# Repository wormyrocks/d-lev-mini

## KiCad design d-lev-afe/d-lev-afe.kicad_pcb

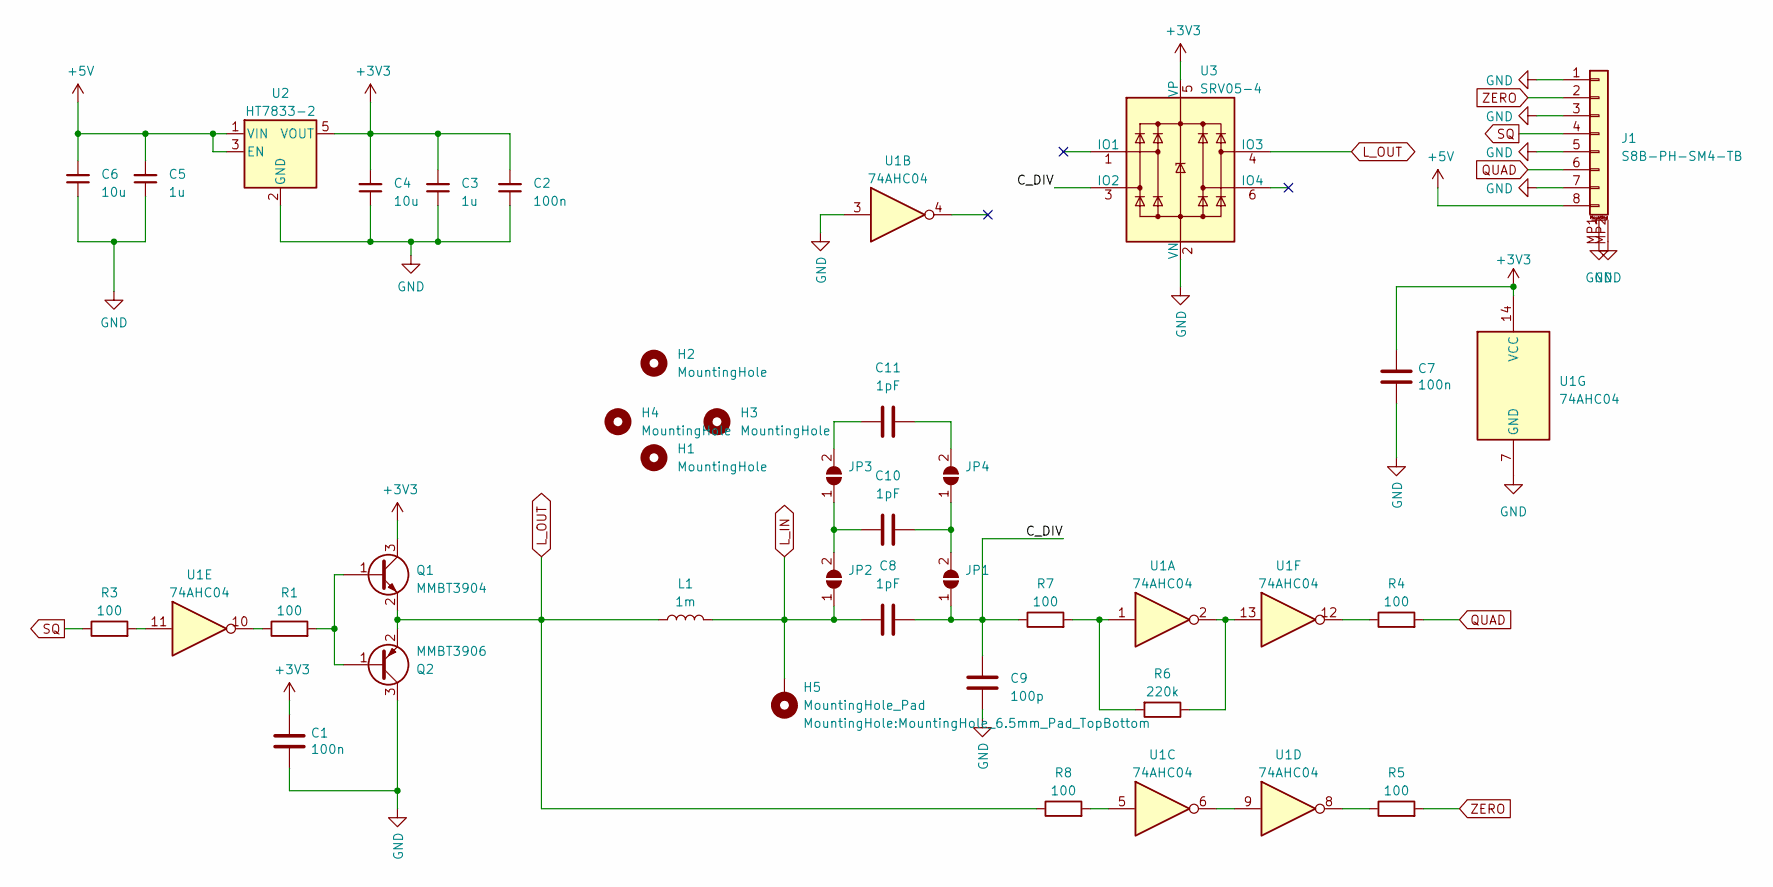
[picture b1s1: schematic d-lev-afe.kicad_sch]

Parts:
C1, C2, C7: 100n; C_0603_1608Metric; MPN GRM188R71E104KA01D; LCSC C14663
C3, C5: 1u; C_0603_1608Metric; LCSC C15849
C4, C6: 10u; C_0805_2012Metric; MPN CL21A106KAYNNNG; LCSC C440198
C8, C10, C11: 1pF; testpoint_cap_1pf
C9: 100p; C_0603_1608Metric; MPN C0603C101K8RACAUTO; LCSC C14858
H1, H2, H3, H4: MountingHole; MountingHole_3.2mm_M3
H5: MountingHole_Pad; MountingHole_6.5mm_Pad_TopBottom
J1: S8B-PH-SM4-TB; JST_PH_S8B-PH-SM4-TB_1x08-1MP_P2.00mm_Horizontal; MPN S8B-PH-SM4-TB; LCSC C265121
JP1, JP2, JP3, JP4: SolderJumper_2_Open; SolderJumper-0.5mm-Tiny
L1: 1m; LargeHoneycombCoil; Tolerance 10%; MPN 2ZFF4-252k-DM
Q1: MMBT3904; SOT-23; MPN MMBT3904-7-F; LCSC C20526
Q2: MMBT3906; SOT-23; MPN MMBT3906-7-F; LCSC C2143
R1, R3, R4, R5, R7, R8: 100; R_0603_1608Metric; LCSC C22775
R6: 220k; R_0603_1608Metric; MPN RC0603FR-13220KL; LCSC C22961
U1: 74AHC04; SOIC-14_3.9x8.7mm_P1.27mm; MPN SN74AHC04DRG4; LCSC C8131
U2: HT7833-2; SOT-23-5; MPN HT7833-2; LCSC C164106
U3: SRV05-4; SOT-23-6; MPN SRV05-4L-TP; LCSC C85364

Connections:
+3V3: C1.1, C2.2, C3.2, C4.2, C7.1, Q1.3 (C), U1.14 (VCC), U2.5 (VOUT), U3.5 (VP)
+5V: C5.2, C6.2, J1.8, U2.1 (VIN), U2.3 (EN)
/C_DIV: C8.1, C9.1, JP1.1 (A), R7.1, U3.3 (IO2)
GND: C1.2, C2.1, C3.1, C4.1, C5.1, C6.1, C7.2, C9.2, J1.1, J1.3, J1.5, J1.7, J1.MP1 (MountPin1), J1.MP2 (MountPin2), Q2.3 (C), U1.3, U1.7 (GND), U2.2 (GND), U3.2 (VN)
L_IN: C8.2, H5.1, JP2.1 (A), L1.2
L_OUT: L1.1, Q1.2 (E), Q2.2 (E), R8.1, U3.4 (IO3)
unnamed: C10.1, JP1.2 (B), JP4.1 (A)
unnamed: C10.2, JP2.2 (B), JP3.1 (A)
unnamed: C11.2, JP3.2 (B)
unnamed: C11.1, JP4.2 (B)
unnamed: Q1.1 (B), Q2.1 (B), R1.2
unnamed: R1.1, U1.10
unnamed: R3.2, U1.11
unnamed: R4.1, U1.12
unnamed: R5.1, U1.8
unnamed: R6.1, U1.2, U1.13
unnamed: R6.2, R7.2, U1.1
unnamed: R8.2, U1.5
unnamed: U1.6, U1.9
QUAD: J1.6, R4.2
SQ: J1.4, R3.1
ZERO: J1.2, R5.2

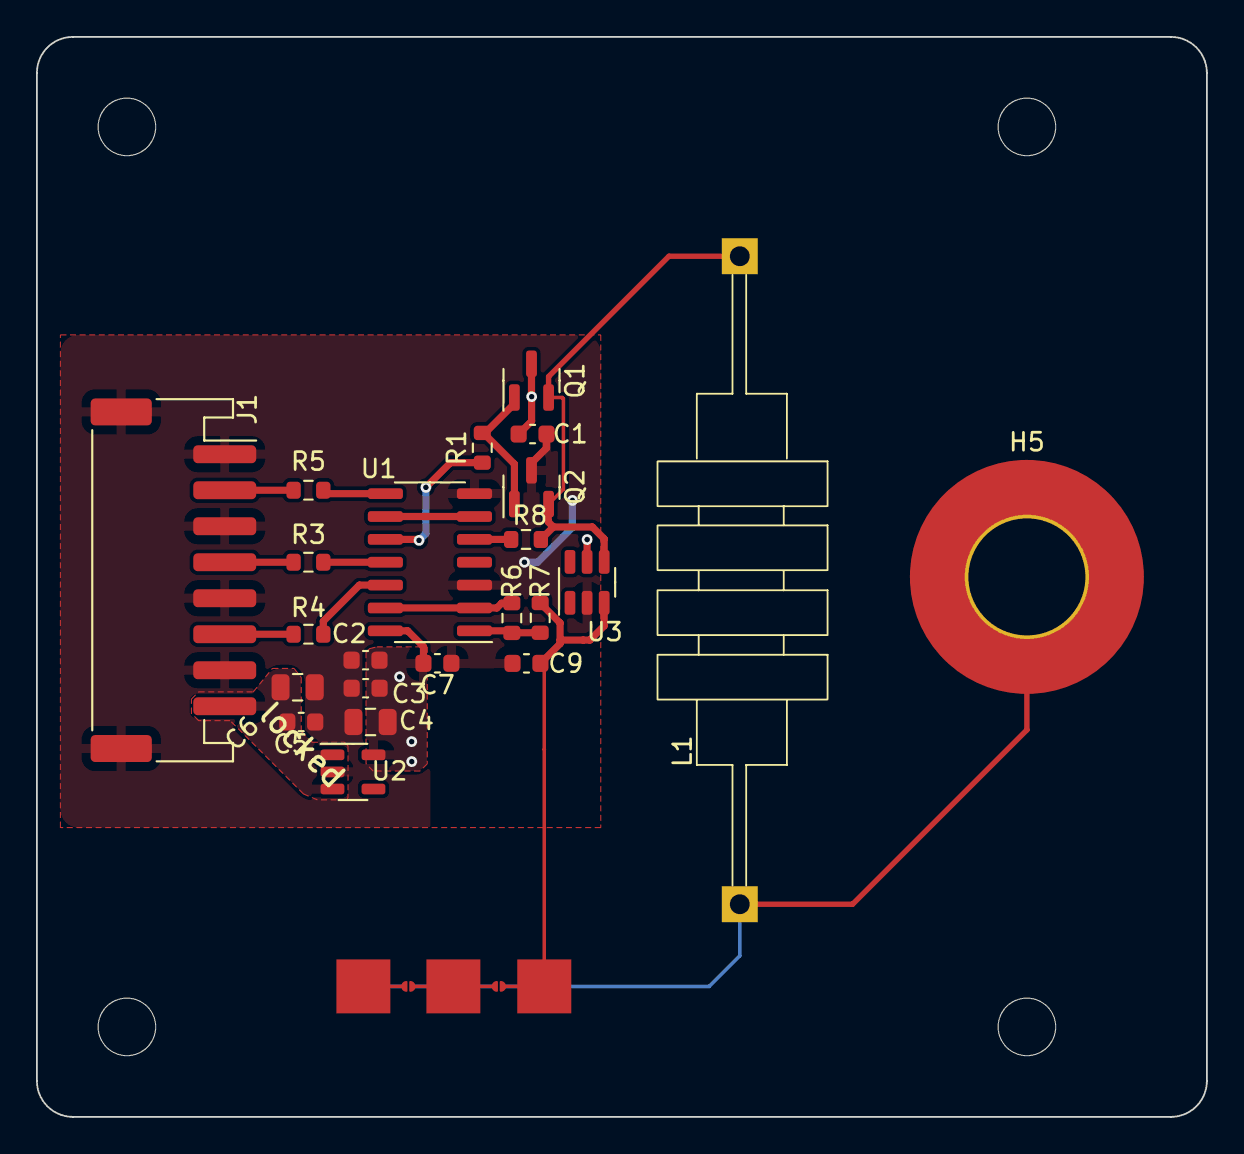
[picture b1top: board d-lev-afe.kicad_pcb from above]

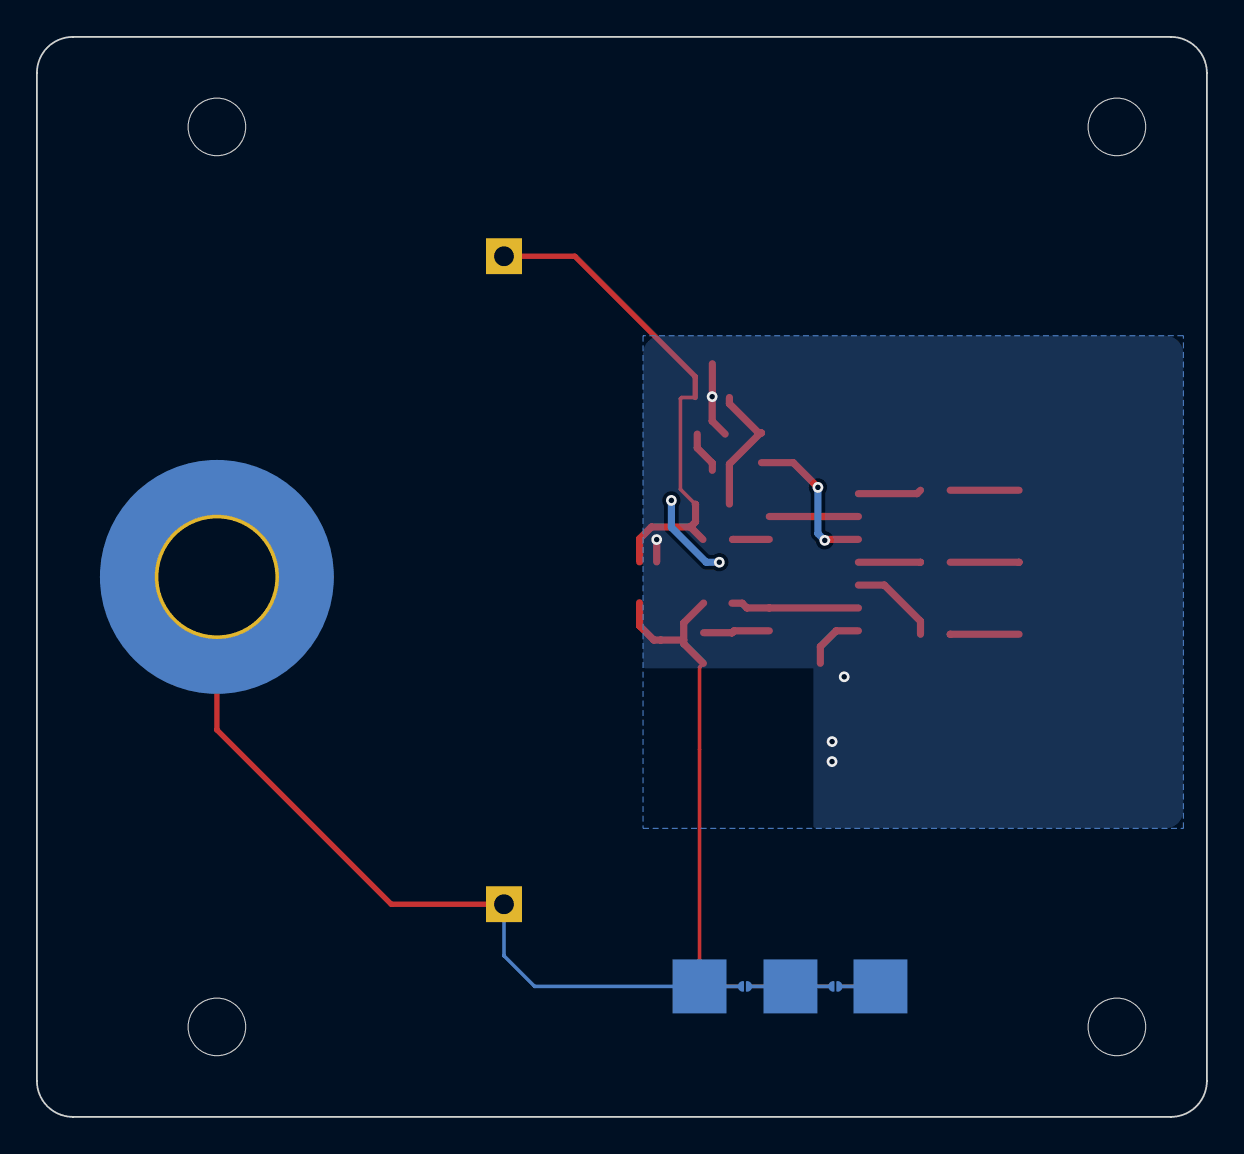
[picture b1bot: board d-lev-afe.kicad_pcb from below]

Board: 2 copper layers, 65.0 x 60.0 mm, 34 parts (2 on the bottom side), 22 nets.

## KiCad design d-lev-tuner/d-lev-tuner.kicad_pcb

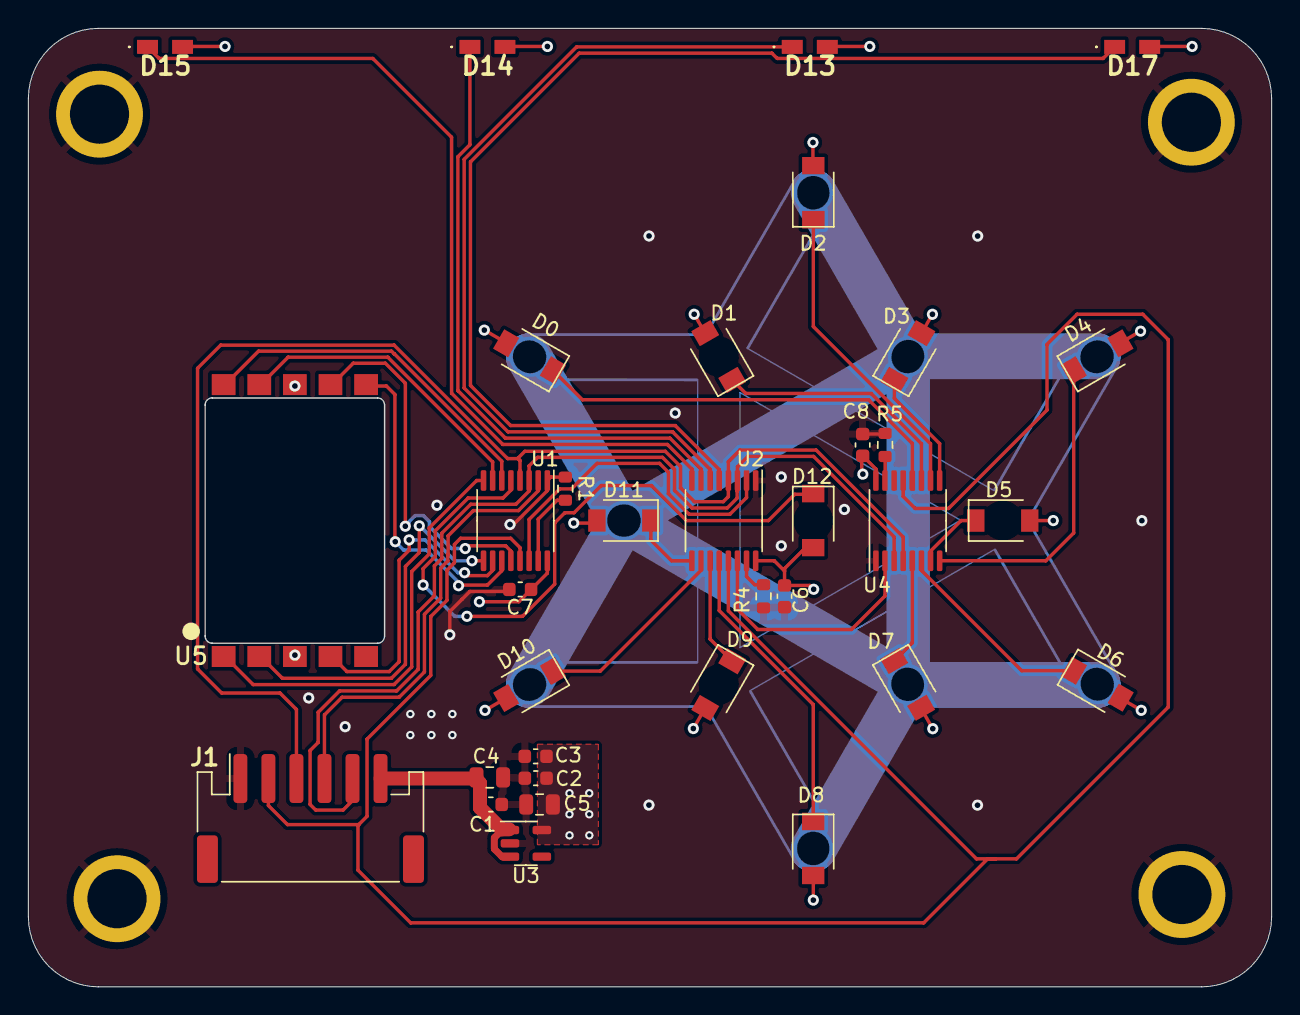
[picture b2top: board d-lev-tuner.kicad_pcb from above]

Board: 4 copper layers, 88.7 x 68.4 mm, 38 parts (0 on the bottom side), 36 nets.

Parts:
C1, C3: 1u; C_0603_1608Metric
C2, C6, C7, C8: 100n; C_0603_1608Metric
C4, C5: 10u; C_0805_2012Metric
D0, D1, D2, D3, D4, D5, D6, D7, D8, D9, D10, D11, D12: LTST-C250TBKT; LED_1206_3216Metric_ReverseMount_Hole1.8x2.4mm
D13, D14, D15, D17: LTST-S220TBKT; S220TBKT
H1, H2, H3, H4: SMTSO-M3-2ET; SMTSO-M3
J1: S6B-PH-SM4-TB; JST_PH_S6B-PH-SM4-TB_1x06-1MP_P2.00mm_Horizontal
R1, R4, R5: 4.7k; R_0603_1608Metric
U1, U2, U4: STP08CP05; TSSOP-16_4.4x5mm_P0.65mm
U3: AP2112K-3.3; SOT-23-5
U5: DSM7TA56

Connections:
+3V3: C2.2, C3.2, C5.2, C6.1, C7.1, C8.1, D0.2 (A), D1.2 (A), D2.2 (A), D3.2 (A), D4.2 (A), D5.2 (A), D6.2 (A), D7.2 (A), D8.2 (A), D9.2 (A), D10.2 (A), D11.2 (A), D12.2 (A), D13.2 (A), D14.2 (A), D15.2 (A), D17.2 (A), U1.16 (VDD), U2.16 (VDD), U3.5 (VOUT), U4.16 (VDD), U5.3 (C.A.), U5.8 (C.A.)
+5V: C1.2, C4.2, J1.6, U3.1 (VIN), U3.3 (EN)
/Net-(U3-SDI): U1.14 (SDO), U2.2 (SDI)
A: U1.12 (OUT7), U5.7 (a)
B: U1.11 (OUT6), U5.6 (b)
C: U1.10 (OUT5), U5.4 (c)
CLK: J1.5, U1.3 (CLK), U2.3 (CLK), U4.3 (CLK)
D: U1.9 (OUT4), U5.2 (d)
E: U1.8 (OUT3), U5.1 (e)
F: U1.7 (OUT2), U5.9 (f)
G: U1.6 (OUT1), U5.10 (g)
GND: C1.1, C2.1, C3.1, C4.1, C5.1, C6.2, C7.2, C8.2, H1.1, H2.1, H3.1, H4.1, J1.1, R1.2, R4.2, R5.2, U1.1 (GND), U2.1 (GND), U3.2 (GND), U4.1 (GND)
LE: J1.3, U1.4 (LE), U2.4 (LE), U4.4 (LE)
LED0: D0.1 (K), U4.12 (OUT7)
LED1: D1.1 (K), U4.11 (OUT6)
LED2: D2.1 (K), U4.10 (OUT5)
LED3: D3.1 (K), U4.9 (OUT4)
LED4: D4.1 (K), U4.8 (OUT3)
LED5: D5.1 (K), U4.7 (OUT2)
LED6: D6.1 (K), U4.6 (OUT1)
LED7: D7.1 (K), U4.5 (OUT0)
LED8: D8.1 (K), U2.12 (OUT7)
LED9: D9.1 (K), U2.11 (OUT6)
LED10: D10.1 (K), U2.10 (OUT5)
LED11: D11.1 (K), U2.9 (OUT4)
LED12: D12.1 (K), U1.5 (OUT0)
LED13: D17.1 (K), U2.5 (OUT0)
LED14: D13.1 (K), U2.6 (OUT1)
LED15: D14.1 (K), U2.7 (OUT2)
LED16: D15.1 (K), U2.8 (OUT3)
unnamed: R1.1, U1.15 (R-EXT)
unnamed: R4.1, U2.15 (R-EXT)
unnamed: U2.14 (SDO), U4.2 (SDI)
unnamed: R5.1, U4.15 (R-EXT)
OE: J1.2, U1.13 (~OE), U2.13 (~OE), U4.13 (~OE)
SDI: J1.4, U1.2 (SDI)

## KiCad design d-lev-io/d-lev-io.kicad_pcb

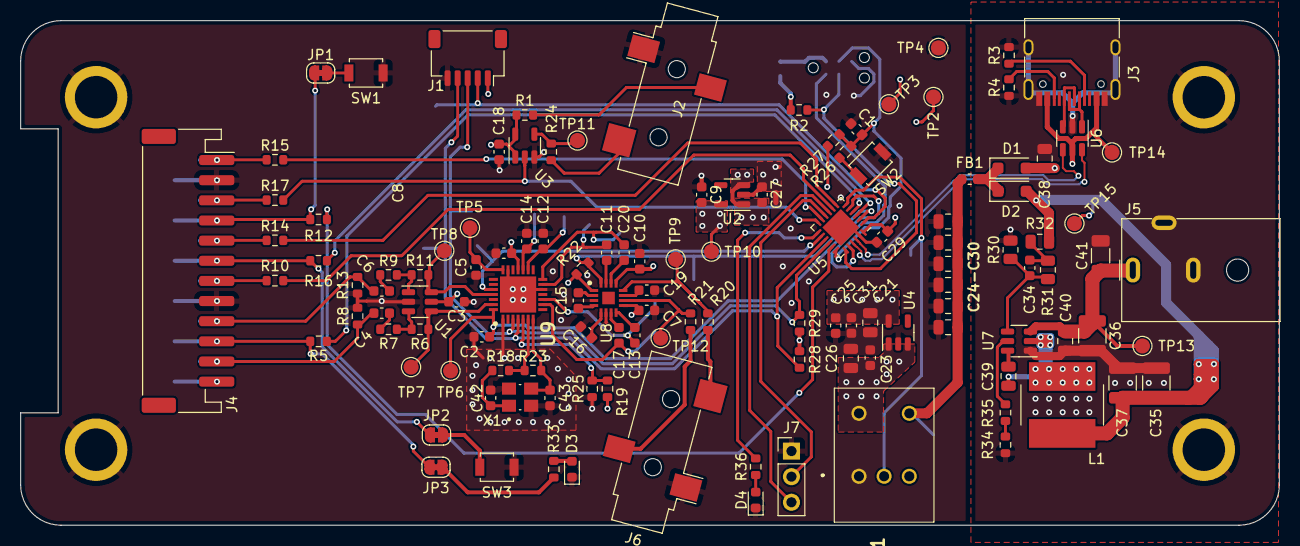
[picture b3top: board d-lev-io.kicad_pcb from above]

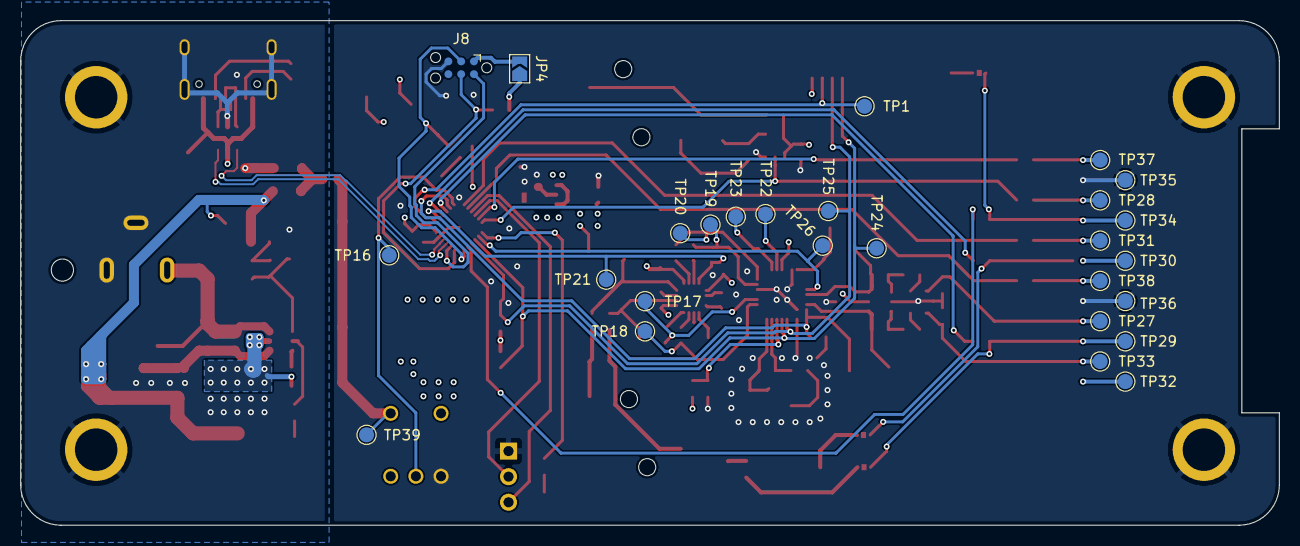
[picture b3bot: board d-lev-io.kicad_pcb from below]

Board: 4 copper layers, 125.0 x 50.1 mm, 155 parts (27 on the bottom side), 89 nets.

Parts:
C1, C21: .1u; C_0603_1608Metric
C2, C7, C8, C9, C10, C12, C14, C15, C16, C23, C27, C31: 1u; C_0603_1608Metric
C3, C18: 100n; C_0603_1608Metric
C4, C6: 4.7n; C_0603_1608Metric
C5, C29: 4.7u; C_0603_1608Metric
C11, C13, C17, C20: .47u; C_0603_1608Metric
C19: 0.1u; C_0603_1608Metric
C22, C24, C25, C26, C28, C30, C32, C33: 10u; C_0805_2012Metric
C34: 75p; C_0603_1608Metric
C35, C37: 22u; C_1210_3225Metric
C36: 10u; C_1210_3225Metric
C38: 0.1u; C_0805_2012Metric
C39, C40: .1u; C_0805_2012Metric
C41: 47u; C_1206_3216Metric
C42, C43: 33p; C_0603_1608Metric
D1, D2: SS34FA; D_SOD-123F
D3: LED; LED_0603_1608Metric
D4: STATUS; LED_0603_1608Metric
FB1: 50mohm DCR, 120R@100Mhz; L_0603_1608Metric
H1, H2, H3, H4: MountingHole_Pad; SMTSO-M3
J1: CV_HDR; JST_SH_SM05B-SRSS-TB_1x05-1MP_P1.00mm_Horizontal
J2: MIDI_OUT_JACK; Jack_3.5mm_CUI_SJ-3523-SMT_Horizontal
J3: USB_C_Receptacle_USB2.0; USB_C_Receptacle_HRO_TYPE-C-31-M-12
J4: Conn_01x12_MountingPin; JST_PH_S12B-PH-SM4-TB_1x12-1MP_P2.00mm_Horizontal
J5: PJ-059A; BarrelJack_CUI_PJ-059A
J6: HEADPHONE; Jack_3.5mm_CUI_SJ-3523-SMT_Horizontal
J7: TOUCH_HDR; PinHeader_1x03_P2.54mm_Vertical
J8: PROG_HDR; Tag-Connect_TC2030-IDC-NL_2x03_P1.27mm_Vertical
JP1: ACAL_JUMPER; SolderJumper-2_P1.3mm_Bridged_RoundedPad1.0x1.5mm
JP2: MUTE_JUMPER; SolderJumper-2_P1.3mm_Bridged_RoundedPad1.0x1.5mm
JP3: MUTE_LED_JUMPER; SolderJumper-2_P1.3mm_Bridged_RoundedPad1.0x1.5mm
JP4: PROG_VIN; SolderJumper-2_P1.3mm_Open_TrianglePad1.0x1.5mm
L1: 15u; L_Bourns_SRN8040TA
NT1: NetTie_2; NetTie-2_SMD_Pad0.5mm
R1, R7, R9, R24: 220; R_0603_1608Metric
R2, R33, R36: 1k; R_0603_1608Metric
R3, R4: 5.1k; R_0603_1608Metric
R5, R12, R15, R16, R25: 0; R_0603_1608Metric
R6, R11, R22: 100k; R_0603_1608Metric
R8, R13: 75; R_0603_1608Metric
R10, R14, R17: 100; R_0603_1608Metric
R18: 20; R_0603_1608Metric
R19: 56k; R_0603_1608Metric
R20, R21: 27; R_0603_1608Metric
R23: 499k; R_0603_1608Metric
R26: 330; R_0603_1608Metric
R27: 10k; R_0603_1608Metric
R28, R29: 2.2k; R_0603_1608Metric
R30: 13.3k; R_0805_2012Metric
R31: 100k; R_0805_2012Metric
R32: 49.9; R_0805_2012Metric
R34: 105k; R_0603_1608Metric
R35: 511k; R_0603_1608Metric
SW1, SW2, SW3: SW_Push; SW_SPST_B3U-1000P
TP1, TP6, TP16, TP21, TP24, TP25, TP26: TestPoint; TestPoint_Pad_D1.5mm
TP2: VSYS; TestPoint_Pad_D1.5mm
TP3: VDD; TestPoint_Pad_D1.5mm
TP4: GND; TestPoint_Pad_D1.5mm
TP5: DVDD; TestPoint_Pad_D1.5mm
TP7, TP8, TP11, TP14, TP27, TP28, TP29, TP30, TP31, TP32, TP33, TP34, TP35, TP36, TP37, TP38: VUSB; TestPoint_Pad_D1.5mm
TP9: SE_L; TestPoint_Pad_D1.5mm
TP10: VCCA; TestPoint_Pad_D1.5mm
TP12: SE_R; TestPoint_Pad_D1.5mm
TP13: VIN; TestPoint_Pad_D1.5mm
TP15: VBUCK; TestPoint_Pad_D1.5mm
TP17: BAL_R-; TestPoint_Pad_D1.5mm
TP18: BAL_R+; TestPoint_Pad_D1.5mm
TP19: BAL_L+; TestPoint_Pad_D1.5mm
TP20: BAL_L-; TestPoint_Pad_D1.5mm
TP22: VREG; TestPoint_Pad_D1.5mm
TP23: VREF; TestPoint_Pad_D1.5mm
TP39: VDD_B4SW; TestPoint_Pad_D1.5mm
U1: 74LVC2GU04; SOT-23-6
U2: ADP151-3.3; SOT-23-5
U3: 74AHC1G126; SOT-23-5
U4: AP2112K-3.3; SOT-23-5
U5: ATSAMD11D14A-M; QFN-24-1EP_4x4mm_P0.5mm_EP2.6x2.6mm
U6: USBLC6-2SC6; SOT-23-6
U7: TPS54202DDC; SOT-23-6
U8: MAX97220C/MAX97220D; QFN50P300X300X80-17N
U9: ES9010K2M; QFN50P500X500X90-29N-D
VR1: RK09711110EL
X1: 7M-50.000MAAJ-T; XTAL_7M-50.000MAAJ-T

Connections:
+3.3VA: C3.2, C7.1, C8.2, C9.2, C10.1, R19.1, R22.2, TP10.1, U1.5 (VCC), U2.5 (VOUT), U8.1 (PVDD), U8.9 (SVDD2), U8.13 (SVDD), U9.18 (VCCA)
+3V3: C21.2, C25.2, C29.2, C31.2, JP4.1 (A), R2.1, R27.1, R28.2, R29.2, TP2.1, U4.5 (VOUT), U5.24 (VDD), VR1.3 (CW)
+12V: C36.1, C40.1, C41.1, J5.1, TP13.1, U7.3 (VIN)
/Buck/VOUT: C35.1, C37.1, D2.2 (A), L1.2, R32.1, TP15.1
/DAC/DAC.XI: C43.1, R23.1, U9.7 (XI(MCLK)), X1.3
/DAC/DAC.XO: R18.2, R23.2, U9.6 (XO)
/DAC/DAC_1V2: C5.1, TP5.1, U9.21 (DVDD)
/DAC/DAC_GPIO: TP26.1, U5.14 (PA17), U9.24 (GPIO1)
/DAC/DAC_RESET: C2.2, TP6.1, U5.5 (PA06), U9.28 (RESETB)
/DAC/HPA_SHDN: R22.1, TP21.1, U5.2 (PA03), U8.16 (~SHDN)
/DAC/IN_BAL.L+: C11.2, U8.15 (INL+)
/DAC/IN_BAL.L-: C20.2, U8.14 (INL-)
/DAC/IN_BAL.R+: C17.2, U8.7 (INR+)
/DAC/IN_BAL.R-: C13.2, U8.8 (INR-)
/DAC/OUT_BAL.L+: C11.1, TP19.1, U9.13 (DACL)
/DAC/OUT_BAL.L-: C20.1, TP20.1, U9.14 (DACLB)
/DAC/OUT_BAL.R+: C17.1, TP18.1, U9.9 (DACR)
/DAC/OUT_BAL.R-: C13.1, TP17.1, U9.10 (DACRB)
/DAC/OUT_SE_L: R20.2, TP9.1, U8.12 (OUTL)
/DAC/OUT_SE_R: R21.2, TP12.1, U8.10 (OUTR)
/DAC/SCL: J1.3, R29.1, TP25.1, U5.16 (PA23), U9.3 (SCL)
/DAC/SDA: J1.4, R28.1, TP24.1, U5.15 (PA22), U9.4 (SDA)
/DAC/SPDIF1: R11.2, TP8.1, U1.6, U9.25 (DATA2)
/DAC/SPDIF2: R6.2, TP7.1, U1.4, U9.27 (DATA_CLK)
/SAMD11/CV_EN: J1.2, TP1.1, U5.1 (PA02)
/SAMD11/JTAG.SWCLK: J8.4, R2.2, U5.19 (PA30/SWCLK)
/SAMD11/JTAG.SWDIO: J8.2, U5.20 (PA31/SWDIO)
/SAMD11/PTC_X2Y8: J7.3, U5.9 (PA10)
/SAMD11/PTC_X3Y9: J7.2, U5.10 (PA11)
/SAMD11/STATUS_LED: R36.2, U5.13 (PA16)
/SAMD11/USB.DN: U5.21 (PA24), U6.6 (I/O1)
/SAMD11/USB.DP: U5.22 (PA25), U6.4 (I/O2)
/SAMD11/VOLUME_POT: TP16.1, U5.6 (PA07), VR1.2 (WIPER)
/SAMD11/~RST: C1.2, J8.3, R26.1, R27.2, U5.18 (PA28/~RST)
/UINN: J3.A7 (D-), J3.B7 (D-), U6.1 (I/O1)
/UINP: J3.A6 (D+), J3.B6 (D+), U6.3 (I/O2)
GND: C1.1, C2.1, C3.1, C5.2, C7.2, C8.1, C9.1, C10.2, C12.1, C14.1, C16.1, C18.1, C19.2, C21.1, C22.1, C23.1, C24.1, C25.1, C26.1, C27.1, C28.1, C29.1, C30.1, C31.1, C32.1, C33.1, C35.2, C36.2, C37.2, C38.1, C40.2, C41.2, C42.2, C43.2, D3.1 (K), D4.1 (K), H1.1, H2.1, H3.1, H4.1, J1.5, J2.S, J3.A1 (GND), J3.A12 (GND), J3.B1 (GND), J3.B12 (GND), J3.S1 (SHIELD), J4.2, J4.8, J5.2, J5.3, J6.S, J7.1, J8.5, NT1.1, NT1.2, R3.1, R4.1, R8.2, R13.2, R25.1, R30.2, R34.2, SW1.1, SW2.1, SW3.1, TP4.1, TP35.1, TP36.1, U1.2 (GND), U2.2 (GND), U3.3 (GND), U4.2 (GND), U5.23 (GND), U5.25 (GND), U6.2 (GND), U7.1 (GND), U8.3 (PGND), U8.6 (SGND), U9.1 (DGND_1), U9.12 (AGND), U9.20 (DGND_2), U9.29 (EP/DGND), VR1.1 (CCW), X1.2 (GND), X1.4 (GND)
unnamed: C4.1, R7.2
unnamed: C6.1, R9.2
unnamed: C34.1, R31.1, R32.2
unnamed: C42.1, R18.1, X1.1
unnamed: D1.1 (K), D2.1 (K), FB1.1
unnamed: D3.2 (A), R33.1
unnamed: D4.2 (A), R36.1
unnamed: J2.R, R1.2
unnamed: J2.T, R24.2
unnamed: J3.A5 (CC1), R3.2
unnamed: J3.B5 (CC2), R4.2
unnamed: J4.1, R15.1, TP37.1
unnamed: J4.3, R17.1, TP28.1
unnamed: J4.5, R14.1, TP31.1
unnamed: J4.7, R10.1, TP38.1
unnamed: J6.R, R21.1
unnamed: J6.T, R20.1
unnamed: J8.1, JP4.2 (B)
unnamed: JP1.2 (B), SW1.2
unnamed: JP2.2 (B), SW3.2
unnamed: JP3.2 (B), R33.2
unnamed: R6.1, R7.1, U1.3
unnamed: R9.1, R11.1, U1.1
unnamed: R24.1, TP11.1, U3.4
unnamed: R26.2, SW2.2
unnamed: R34.1, R35.2
unnamed: R16.1, U5.3 (PA04)
unnamed: R5.1, U5.4 (PA05)
unnamed: R12.1, U5.17 (PA27)
unnamed: C39.1, U7.6 (BOOT)
unnamed: R35.1, U7.5 (EN)
unnamed: C34.2, R30.1, R31.2, U7.4 (FB)
unnamed: C39.2, L1.1, U7.2 (SW)
unnamed: C19.1, U8.11 (BIAS)
unnamed: C15.2, U8.4 (C1N)
unnamed: C15.1, U8.2 (C1P)
unnamed: C16.2, U8.5 (PVSS)
unnamed: R19.2, R25.2, U9.5 (ADDR)
unnamed: C12.2, TP23.1, U9.16 (VREF)
unnamed: C14.2, TP22.1, U9.17 (VREG)
SWITCH_LOW: C22.2, C24.2, C28.2, C30.2, C32.2, C33.2, FB1.2, TP39.1, VR1.5 (NO)
VBUS: C38.2, D1.2 (A), J3.A4 (VBUS), J3.A9 (VBUS), J3.B4 (VBUS), J3.B9 (VBUS), TP14.1, U6.5 (VBUS)
VDD: C18.2, C23.2, C26.2, C27.2, J1.1, J4.12, R1.1, TP3.1, TP32.1, U2.1 (VIN), U2.3 (EN), U3.1, U3.5 (VCC), U4.1 (VIN), U4.3 (EN), VR1.4 (COM)
acal_btn: J4.4, JP1.1 (A), R12.2, TP34.1
midi_from_fpga_3v: R17.2, U3.2, U5.12 (PA15)
midi_to_fpga_3v: R15.2, U5.11 (PA14)
mute_btn: J4.6, JP2.1 (A), R16.2, TP30.1
mute_led: J4.10, JP3.1 (A), R5.2, TP29.1
spdif_line: C6.2, J4.9, R13.1, TP27.1
spdif_mon: C4.2, J4.11, R8.1, TP33.1
uart_rx_3v: R10.2, U5.8 (PA09/XOUT)
uart_tx_3v: R14.2, U5.7 (PA08/XIN)

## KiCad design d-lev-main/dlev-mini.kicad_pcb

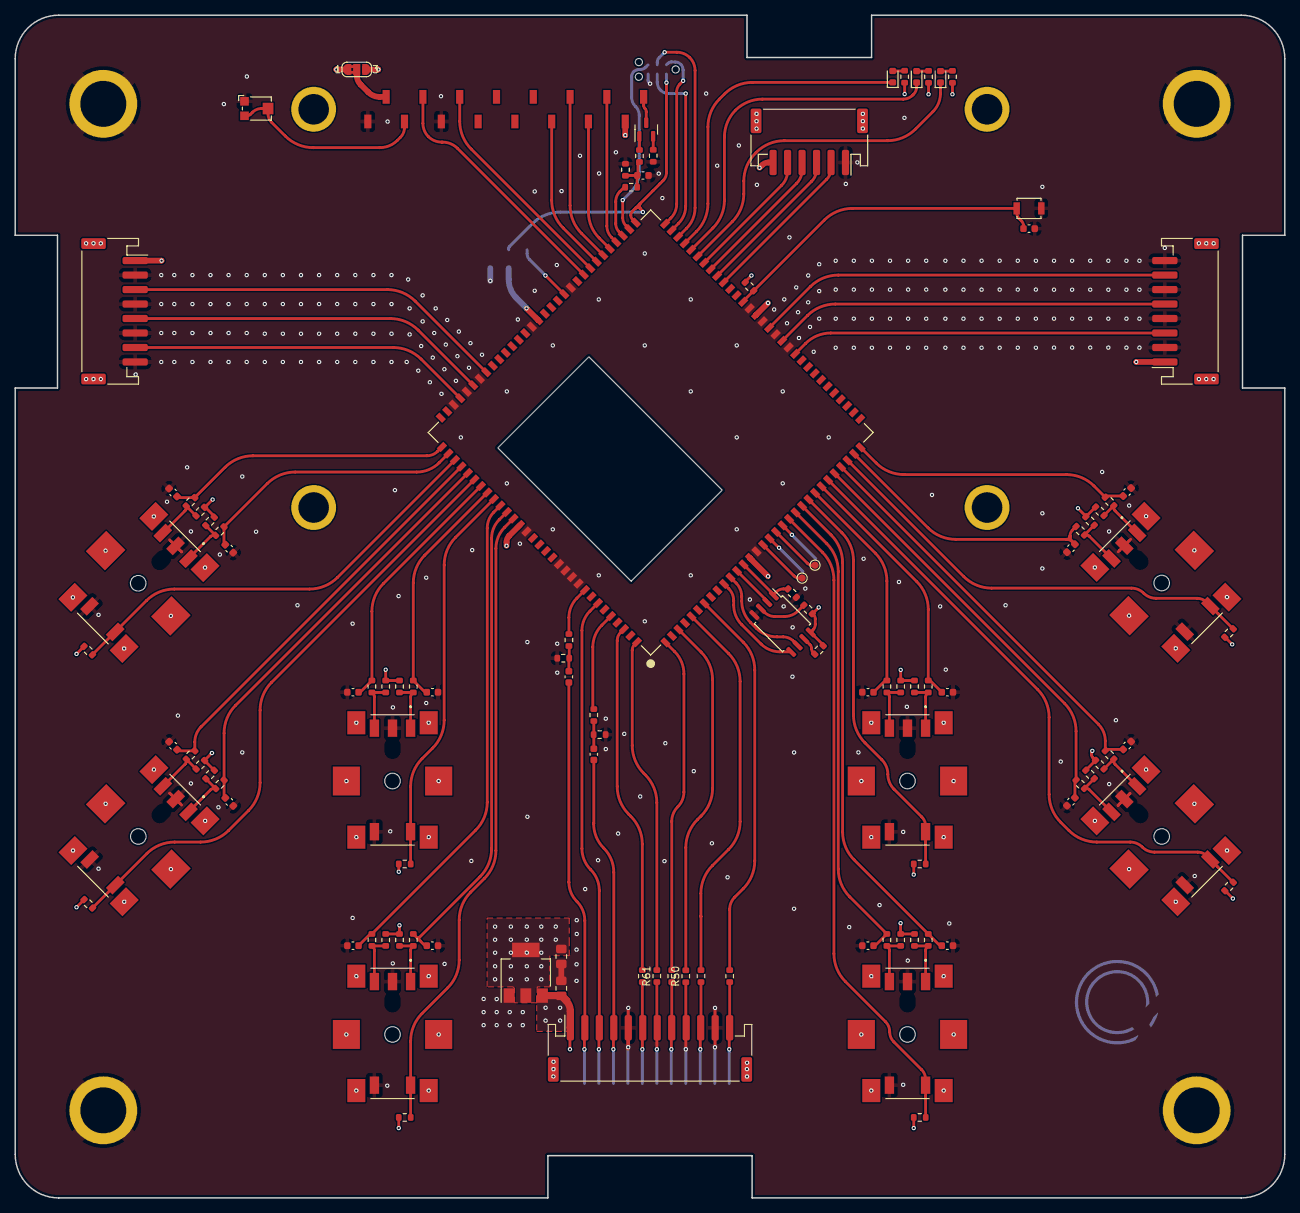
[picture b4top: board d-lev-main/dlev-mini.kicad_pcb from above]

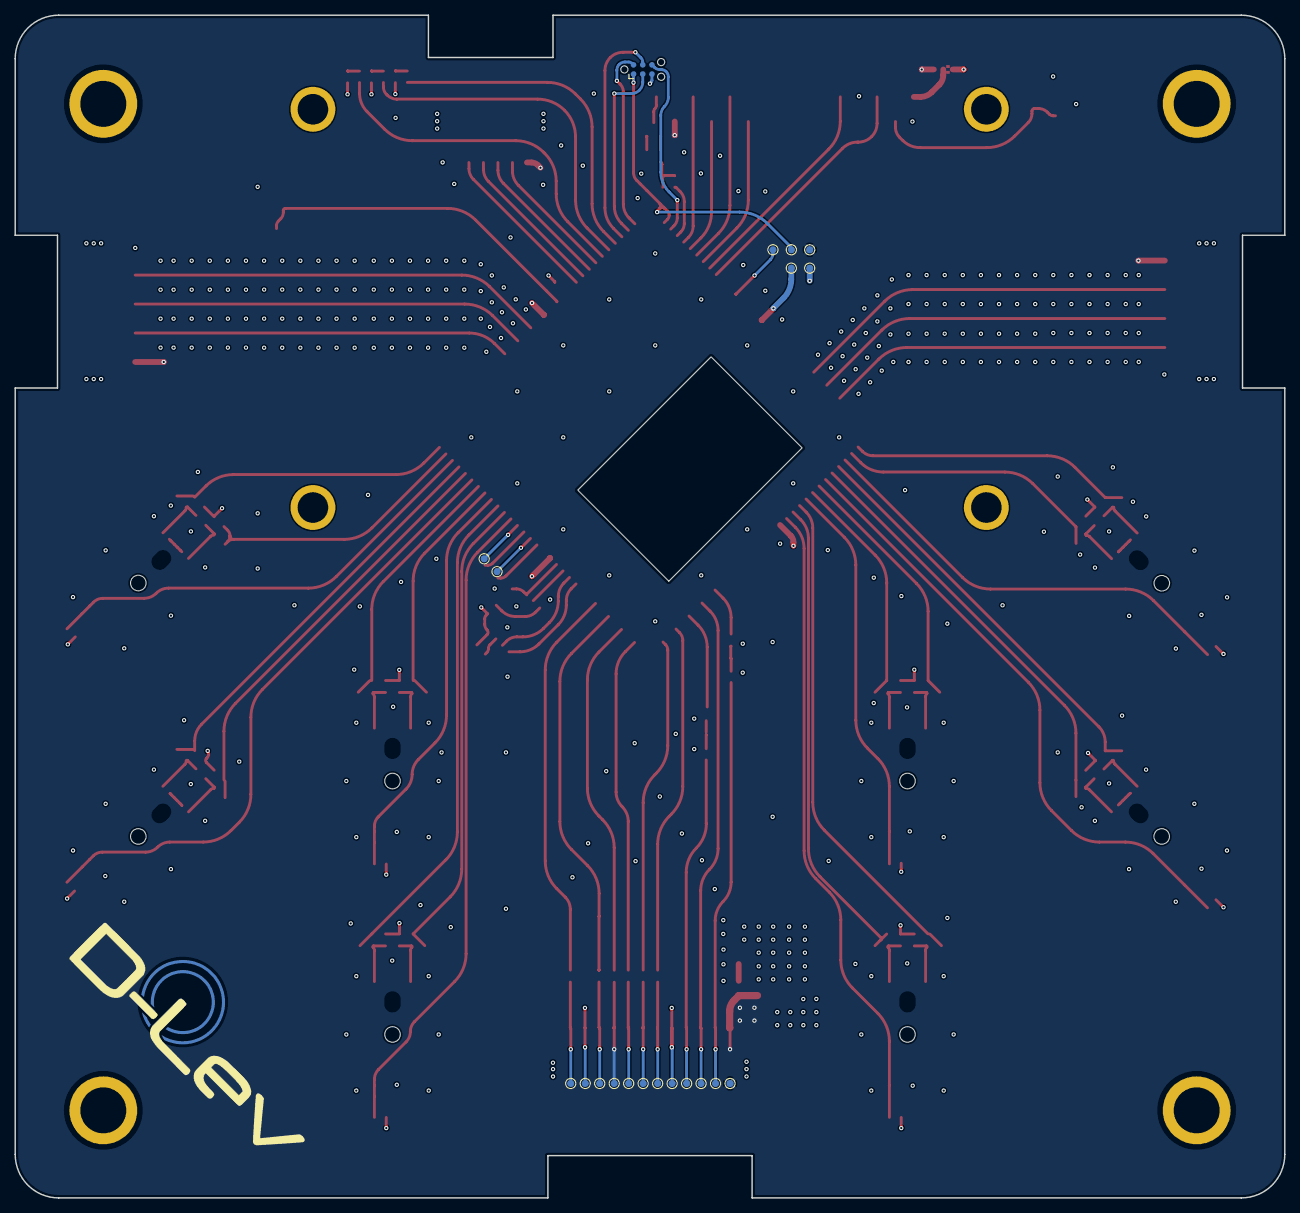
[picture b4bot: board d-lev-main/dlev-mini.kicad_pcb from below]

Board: 4 copper layers, 175.3 x 163.3 mm, 136 parts (20 on the bottom side), 108 nets.

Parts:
C1: .1u; C_0603_1608Metric
C2, C3, C4, C6, C7, C8, C9, C10, C11, C13, C14, C15, C16, C17, C18, C21, C22: .01u; C_0603_1608Metric
C5, C12: 100n; C_0603_1608Metric
C19, C20: 22u; C_0805_2012Metric_Pad1.18x1.45mm_HandSolder
D1, D2, D3: LED; LED_0603_1608Metric
DS1: LCD-20X4B-noshield; ERM2004-2
H1, H2, H7, H8: MountingHole_Pad; SMTSO-M4
H3, H4, H5, H6: M3 Standoff; SMTSO-M3
J1: S6B-PH-SM4-TB; JST_PH_S6B-PH-SM4-TB_1x06-1MP_P2.00mm_Horizontal
J2, J3: S8B-PH-SM4-TB; JST_PH_S8B-PH-SM4-TB_1x08-1MP_P2.00mm_Horizontal
J4: S12B-PH-SM4-TB; JST_PH_S12B-PH-SM4-TB_1x12-1MP_P2.00mm_Horizontal
J5: Tag-Connect TC2030-NL; Tag-Connect_TC2030-IDC-NL_2x03_P1.27mm_Vertical
JP1: LCD_VSEL; SolderJumper-3_P1.3mm_Bridged2Bar12_RoundedPad1.0x1.5mm_Num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
Q1: MMBT3904; SOT-23
R1, R2, R3, R4, R6, R7: 1k; R_0603_1608Metric
R5: 22; R_0603_1608Metric
R8, R9, R10, R11, R12, R13, R14, R15, R16, R17, R18, R19, R20, R21, R22, R23, R24, R25, R26, R27, R28, R29, R36, R37, R38, R39, R40, R41, R42, R43, R44, R45, R46, R47, R48, R49, R51, R52, R53, R54, R55, R56, R57, R58: 10k; R_0603_1608Metric
R30, R32: 210; R_0603_1608Metric
R31, R33: 110; R_0603_1608Metric
R34, R35, R50, R59, R61: 100; R_0603_1608Metric
R60: 0; R_0603_1608Metric
RV1: 10K; Potentiometer_Bourns_TC33X_Vertical
SW1: SW_Push; SW_SPST_B3U-1000P
SW2, SW3, SW4, SW5, SW6, SW7, SW9, SW10: RotaryEncoder_Switch; PEC11S-929K
TP1: GPIO_O3; TestPoint_Pad_D1.0mm
TP2: GPIO_I3; TestPoint_Pad_D1.0mm
TP3: 2v5; TestPoint_Pad_D1.0mm
TP4: VDD; TestPoint_Pad_D1.0mm
TP5: GND; TestPoint_Pad_D1.0mm
TP6: 1v2; TestPoint_Pad_D1.0mm
TP7: 3v3; TestPoint_Pad_D1.0mm
TP8: GPIO_O2; TestPoint_Pad_D1.0mm
TP9: GPIO_I2; TestPoint_Pad_D1.0mm
TP10, TP11, TP12, TP13, TP14, TP15, TP16, TP17, TP18, TP19, TP20, TP21: TestPoint; TestPoint_Pad_D1.0mm
U1: AC608; ac608-toponly
U2: 25LCxxx; SOIC-8_5.275x5.275mm_P1.27mm
U3: AMS1117-3.3; SOT-223-3_TabPin2

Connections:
+2V5: J5.1, TP3.1, U1.63 (VDD2.5)
+3V3: C19.1, JP1.1 (A), R1.2, R2.2, R3.2, R8.2, R9.1, R11.1, R13.1, R14.2, R16.2, R17.1, R18.1, R21.1, R24.1, R25.1, R26.1, R28.1, R37.1, R39.1, R40.1, R43.1, R44.1, R46.1, R47.1, R49.1, R52.1, R53.1, R54.1, R56.1, R57.1, R58.1, TP7.1, U1.14 (VDD3.3), U1.48 (VDD3.3), U1.78 (VDD3.3), U1.106 (VDD3.3), U2.8 (VCC), U3.2 (VO)
/FPGA/TCK: J5.4, U1.60 (TCK)
/FPGA/TDI: J5.3, U1.61 (TDI)
/FPGA/TDO: J5.6, U1.64 (TDO)
/FPGA/TMS: J5.2, U1.62 (TMS)
/FPGA/enc_1.a: C3.1, R12.1, U1.95 (LVDS_TX4_P)
/FPGA/enc_1.b: C4.1, R10.1, U1.94 (LVDS_TX4_N)
/FPGA/enc_1.s: R9.2, SW2.S1, U1.96 (LVDS_TX5_N)
/FPGA/enc_2.a: C9.1, R23.1, U1.98 (IO_R1)
/FPGA/enc_2.b: C8.1, R22.1, U1.97 (LVDS_TX5_P)
/FPGA/enc_2.s: R44.2, SW4.S1, U1.99 (IO_T2)
/FPGA/enc_3.a: C11.1, R27.1, U1.101 (IO_T3)
/FPGA/enc_3.b: C10.1, R29.1, U1.100 (IO_R3)
/FPGA/enc_3.s: R49.2, SW5.S1, U1.102 (IO_R4)
/FPGA/enc_4.a: C17.1, R45.1, U1.104 (IO_R5)
/FPGA/enc_4.b: C18.1, R48.1, U1.103 (IO_T4)
/FPGA/enc_4.s: R57.2, SW9.S1, U1.105 (IO_T5)
/FPGA/enc_5.a: C6.1, R20.1, U1.31 (IO_D15)
/FPGA/enc_5.b: C7.1, R19.1, U1.30 (IO_D16)
/FPGA/enc_5.s: R21.2, SW3.S1, U1.29 (I_E16)
/FPGA/enc_6.a: C15.1, R42.1, U1.28 (IO_F15)
/FPGA/enc_6.b: C16.1, R41.1, U1.27 (IO_G15)
/FPGA/enc_6.s: R56.2, SW7.S1, U1.26 (IO_F16)
/FPGA/enc_7.a: C14.1, R36.1, U1.25 (IO_K15)
/FPGA/enc_7.b: C13.1, R38.1, U1.24 (IO_J14)
/FPGA/enc_7.s: R52.2, SW6.S1, U1.23 (IO_L14)
/FPGA/enc_8.a: C22.1, R51.1, U1.22 (IO_J16)
/FPGA/enc_8.b: C21.1, R55.1, U1.21 (IO_J15)
/FPGA/enc_8.s: R58.2, SW10.S1, U1.20 (IO_K16)
/FPGA/gpio_i2: TP9.1, U1.19 (IO_L13)
/FPGA/gpio_i3: TP2.1, U1.18 (IO_N14)
/FPGA/gpio_o2: TP8.1, U1.17 (IO_P14)
/FPGA/gpio_o3: TP1.1, U1.16 (IO_N12)
/FPGA/lcd.data0: DS1.11 (DB4), U1.69 (IO_N5)
/FPGA/lcd.data1: DS1.12 (DB5), U1.68 (IO_N3)
/FPGA/lcd.data2: DS1.13 (DB6), U1.67 (IO_M6)
/FPGA/lcd.data3: DS1.14 (DB7), U1.66 (IO_L4)
/FPGA/lcd.e: DS1.6 (E), U1.70 (IO_P3)
/FPGA/lcd.pwm: R6.1, U1.65 (IO_K5)
/FPGA/lcd.rs: DS1.4 (RS), U1.71 (IO_L7)
/FPGA/led1: D2.1 (K), U1.57 (IO_G5)
/FPGA/led2: D3.1 (K), U1.58 (IO_G2)
/FPGA/led3: D1.1 (K), U1.59 (IO_G1)
/FPGA/mem_spi.cl: U1.11 (IO_L16), U2.6 (SCK)
/FPGA/mem_spi.cs: R15.1, U1.13 (IO_N11), U2.1 (~CS)
/FPGA/mem_spi.di: U1.10 (IO_L15), U2.5 (MOSI)
/FPGA/mem_spi.do: U1.12 (IO_P11), U2.2 (MISO)
/FPGA/pitch.quad: J2.3, U1.86 (LVDS_TX1_N)
/FPGA/pitch.sq: J2.5, U1.88 (LVDS_TX2_N)
/FPGA/pitch.zero: J2.7, U1.90 (LVDS_TX3_N)
/FPGA/tuner.le: J1.3, U1.54 (IO_F3)
/FPGA/tuner.oe: J1.2, U1.53 (IO_D1)
/FPGA/tuner.scl: J1.5, U1.56 (IO_F1)
/FPGA/tuner.sda: J1.4, U1.55 (IO_F2)
/FPGA/vol.quad: J3.3, U1.42 (I_A9)
/FPGA/vol.sq: J3.5, U1.44 (IO_C9)
/FPGA/vol.zero: J3.7, U1.46 (IO_D9)
/FPGA/~reset: C2.1, R8.1, SW1.1, U1.50 (I_E1)
/LCD/VLCD: DS1.2 (VDD), JP1.2 (C)
/LCD/backlight_cathode: DS1.16 (K), Q1.3 (C)
/encoder1/A1: R23.2, R25.2, SW4.A
/encoder1/B1: R22.2, R24.2, SW4.B
/encoder2/A1: R26.2, R27.2, SW5.A
/encoder2/B1: R28.2, R29.2, SW5.B
/encoder3/A1: R45.2, R47.2, SW9.A
/encoder3/B1: R46.2, R48.2, SW9.B
/encoder4/A1: R17.2, R20.2, SW3.A
/encoder4/B1: R18.2, R19.2, SW3.B
/encoder5/A1: R40.2, R42.2, SW7.A
/encoder5/B1: R41.2, R43.2, SW7.B
/encoder6/A1: R36.2, R39.2, SW6.A
/encoder6/B1: R37.2, R38.2, SW6.B
/encoder7/A1: R51.2, R53.2, SW10.A
/encoder7/B1: R54.2, R55.2, SW10.B
/encoder/A1: R11.2, R12.2, SW2.A
/encoder/B1: R10.2, R13.2, SW2.B
/spdif_tx_0: R30.1, U1.120 (IO_R12)
/spdif_tx_1: R32.1, U1.116 (IO_R10)
GND: C1.2, C2.2, C3.2, C4.2, C6.2, C7.2, C8.2, C9.2, C10.2, C11.2, C13.2, C14.2, C15.2, C16.2, C17.2, C18.2, C19.2, C20.2, C21.2, C22.2, DS1.1 (VSS), DS1.5 (R/W), H1.1, H2.1, H7.1, H8.1, J1.1, J2.2, J2.4, J2.6, J2.8, J3.2, J3.4, J3.6, J3.8, J4.5, J4.11, J5.5, R4.1, R5.1, R15.2, R31.1, R33.1, RV1.1, SW1.2, SW2.C, SW2.S2, SW3.C, SW3.S2, SW4.C, SW4.S2, SW5.C, SW5.S2, SW6.C, SW6.S2, SW7.C, SW7.S2, SW9.C, SW9.S2, SW10.C, SW10.S2, TP5.1, TP14.1, TP20.1, U1.15 (GND), U1.43 (I_B9), U1.45 (I_A8), U1.47 (I_B8), U1.49 (GND), U1.73 (GND), U1.79 (GND), U1.87 (LVDS_TX1_P), U1.89 (LVDS_TX2_P), U1.91 (LVDS_TX3_P), U1.107 (GND), U1.112 (I_R8), U1.113 (I_T8), U1.114 (I_R9), U1.115 (I_T9), U2.4 (GND), U3.1 (GND)
unnamed: C1.1, R4.2, R6.2, R7.1
unnamed: C5.1, R32.2, R33.2
unnamed: C12.1, R30.2, R31.2
unnamed: D1.2 (A), R3.1
unnamed: D2.2 (A), R1.1
unnamed: D3.2 (A), R2.1
unnamed: DS1.3 (V0), RV1.2, RV1.3
unnamed: J4.6, R34.1, TP15.1
unnamed: J4.7, R61.1, TP16.1
unnamed: J4.8, R35.1, TP17.1
unnamed: J4.9, R50.1, TP18.1
unnamed: J4.10, R59.1, TP19.1
unnamed: J4.12, R60.1, TP21.1
unnamed: Q1.1 (B), R7.2
unnamed: Q1.2 (E), R5.2
unnamed: TP6.1, U1.74 (VDD1.2)
unnamed: R16.1, U2.7 (~HOLD)
unnamed: R14.1, U2.3 (~WP)
VDD: C20.1, DS1.15 (A), J1.6, J2.1, J3.1, J4.1, JP1.3 (B), TP4.1, TP10.1, U3.3 (VI)
acal_btn: R50.2, U1.3 (IO_R16)
midi_in: R60.2, U1.7 (IO_N16)
midi_out: R59.2, U1.5 (IO_P16)
mute_btn: R61.2, U1.124 (IO_R14)
mute_led: J4.3, TP12.1, U1.118 (IO_R11)
spdif_line: C12.2, J4.4, TP13.1
spdif_mon: C5.2, J4.2, TP11.1
uart_rx: R35.2, U1.1 (IO_T14)
uart_tx: R34.2, U1.122 (IO_R13)
